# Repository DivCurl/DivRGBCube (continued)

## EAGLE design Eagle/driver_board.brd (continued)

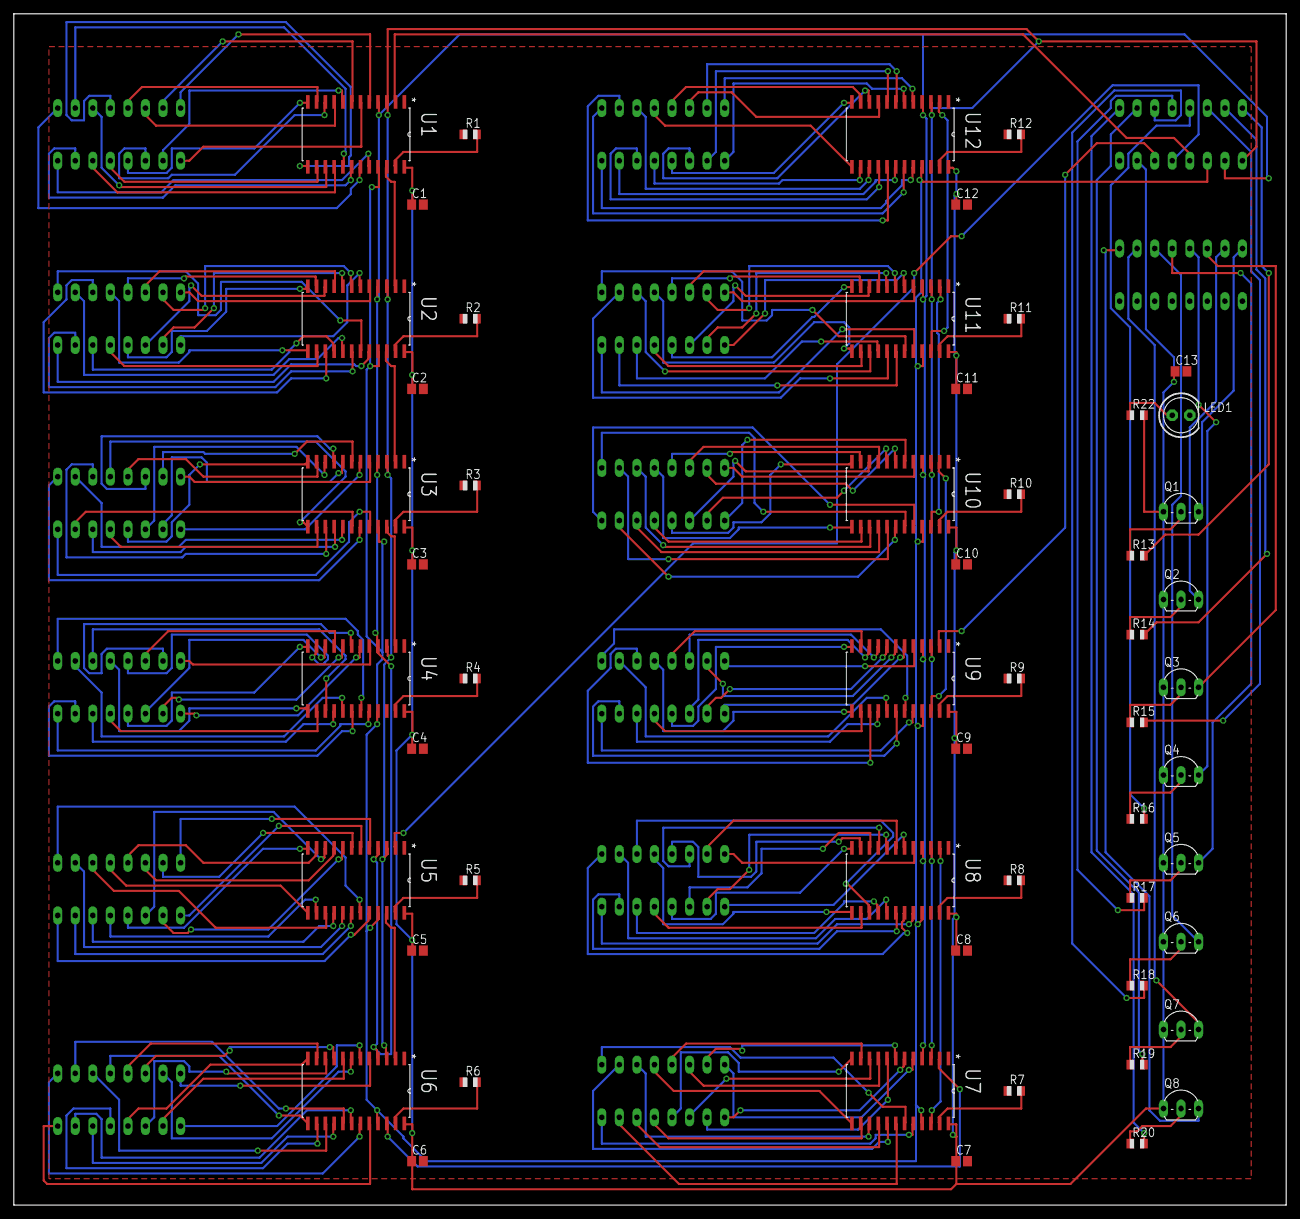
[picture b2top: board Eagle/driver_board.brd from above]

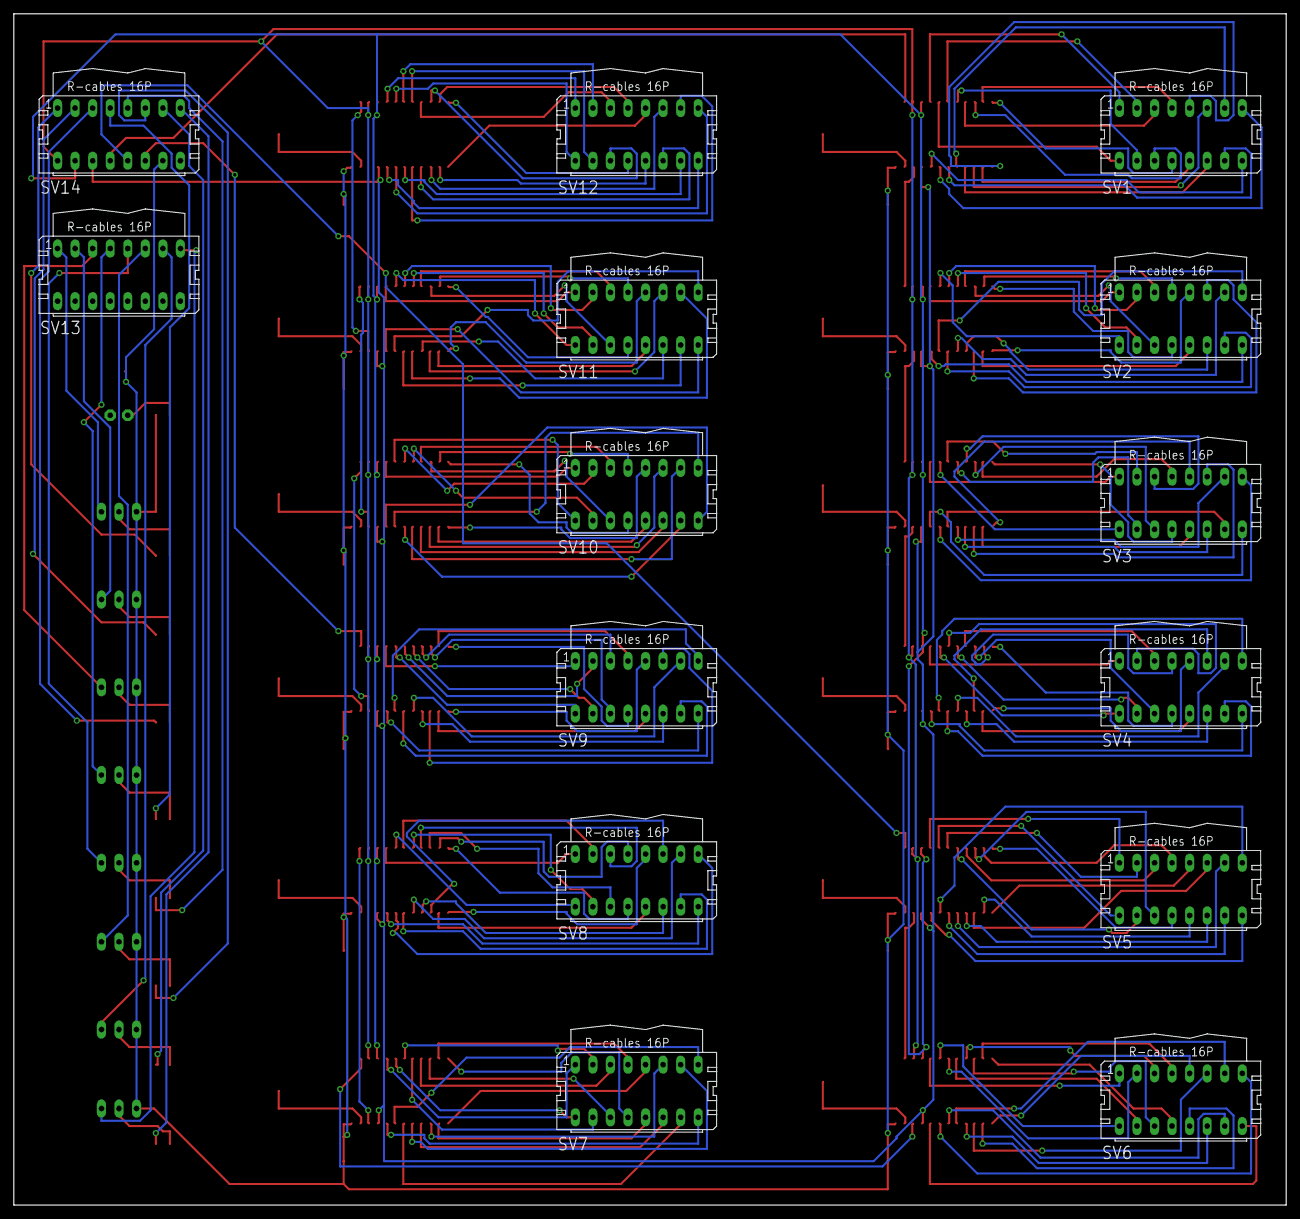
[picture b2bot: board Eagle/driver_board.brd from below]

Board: 2 copper layers, 184.1 x 172.4 mm, 69 parts (14 on the bottom side), 246 nets.

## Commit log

2013-10-29 Driver Board Commit
    Initial Commit of Driver Board (rev0)
2013-11-01 Revert "Driver Board Commit"
    This reverts commit d0ab9ee2da23c5bfc241576f39f64d58649d03a1.
2013-11-01 Driver Board - Final Design Draft
2013-11-04 Driver Board - Production Release
    final board layout - release for production
2013-12-01 Test Build - 0.5
    Source Commit - Basic functionality and hardware testing complete. Two
    basic animations tested and functional.
    TODO: BCM bugfixes, timer stuff, color fill stuff
2013-12-06 Test Build 0.8
    Core functionality tested and debugged with some major additions.
    Currently stable and working to satisfaction, more minor tweaks being
    done here and there. BCM, core color fading, and basic animation code
    completed.
    TODO: Complete and test more animations, improve color fade handling and
    mode settings
2013-12-06 Pics
    Construction Progress Pics
2013-12-09 Build 0.85
    Additional improvements to color fading code. Currently 4 working
    animations. TODO: more animations, further tweak and improve color
    fading modes and operation.
2013-12-28 Build 0.9
    Added:
    1. Text generation engine and drawing modes
    2. General purpose matrix transformation engine -- this was alot of work
    to get working but it finally paid off. Looking forward to use it in new
    animations...
    3. Bresenham algorithm (modified) for easier line drawing
2014-05-28 Build 0.95
    1. Completely revised and organized code structure and layout
    2. Added LCD interface
    3. Added spectrum analyzer (still WIP - works well but needs a little
    tuning)
    4. Added a few new animations
2014-06-03 Build 0.98
    1. Further improvements to code organization and structure
    2. Several changes to include new LCD touch screen functionality and
    flow control
    3. Bug fixes for various animations
    4. Timing tweaks (still a little work to do here to unify timings)
